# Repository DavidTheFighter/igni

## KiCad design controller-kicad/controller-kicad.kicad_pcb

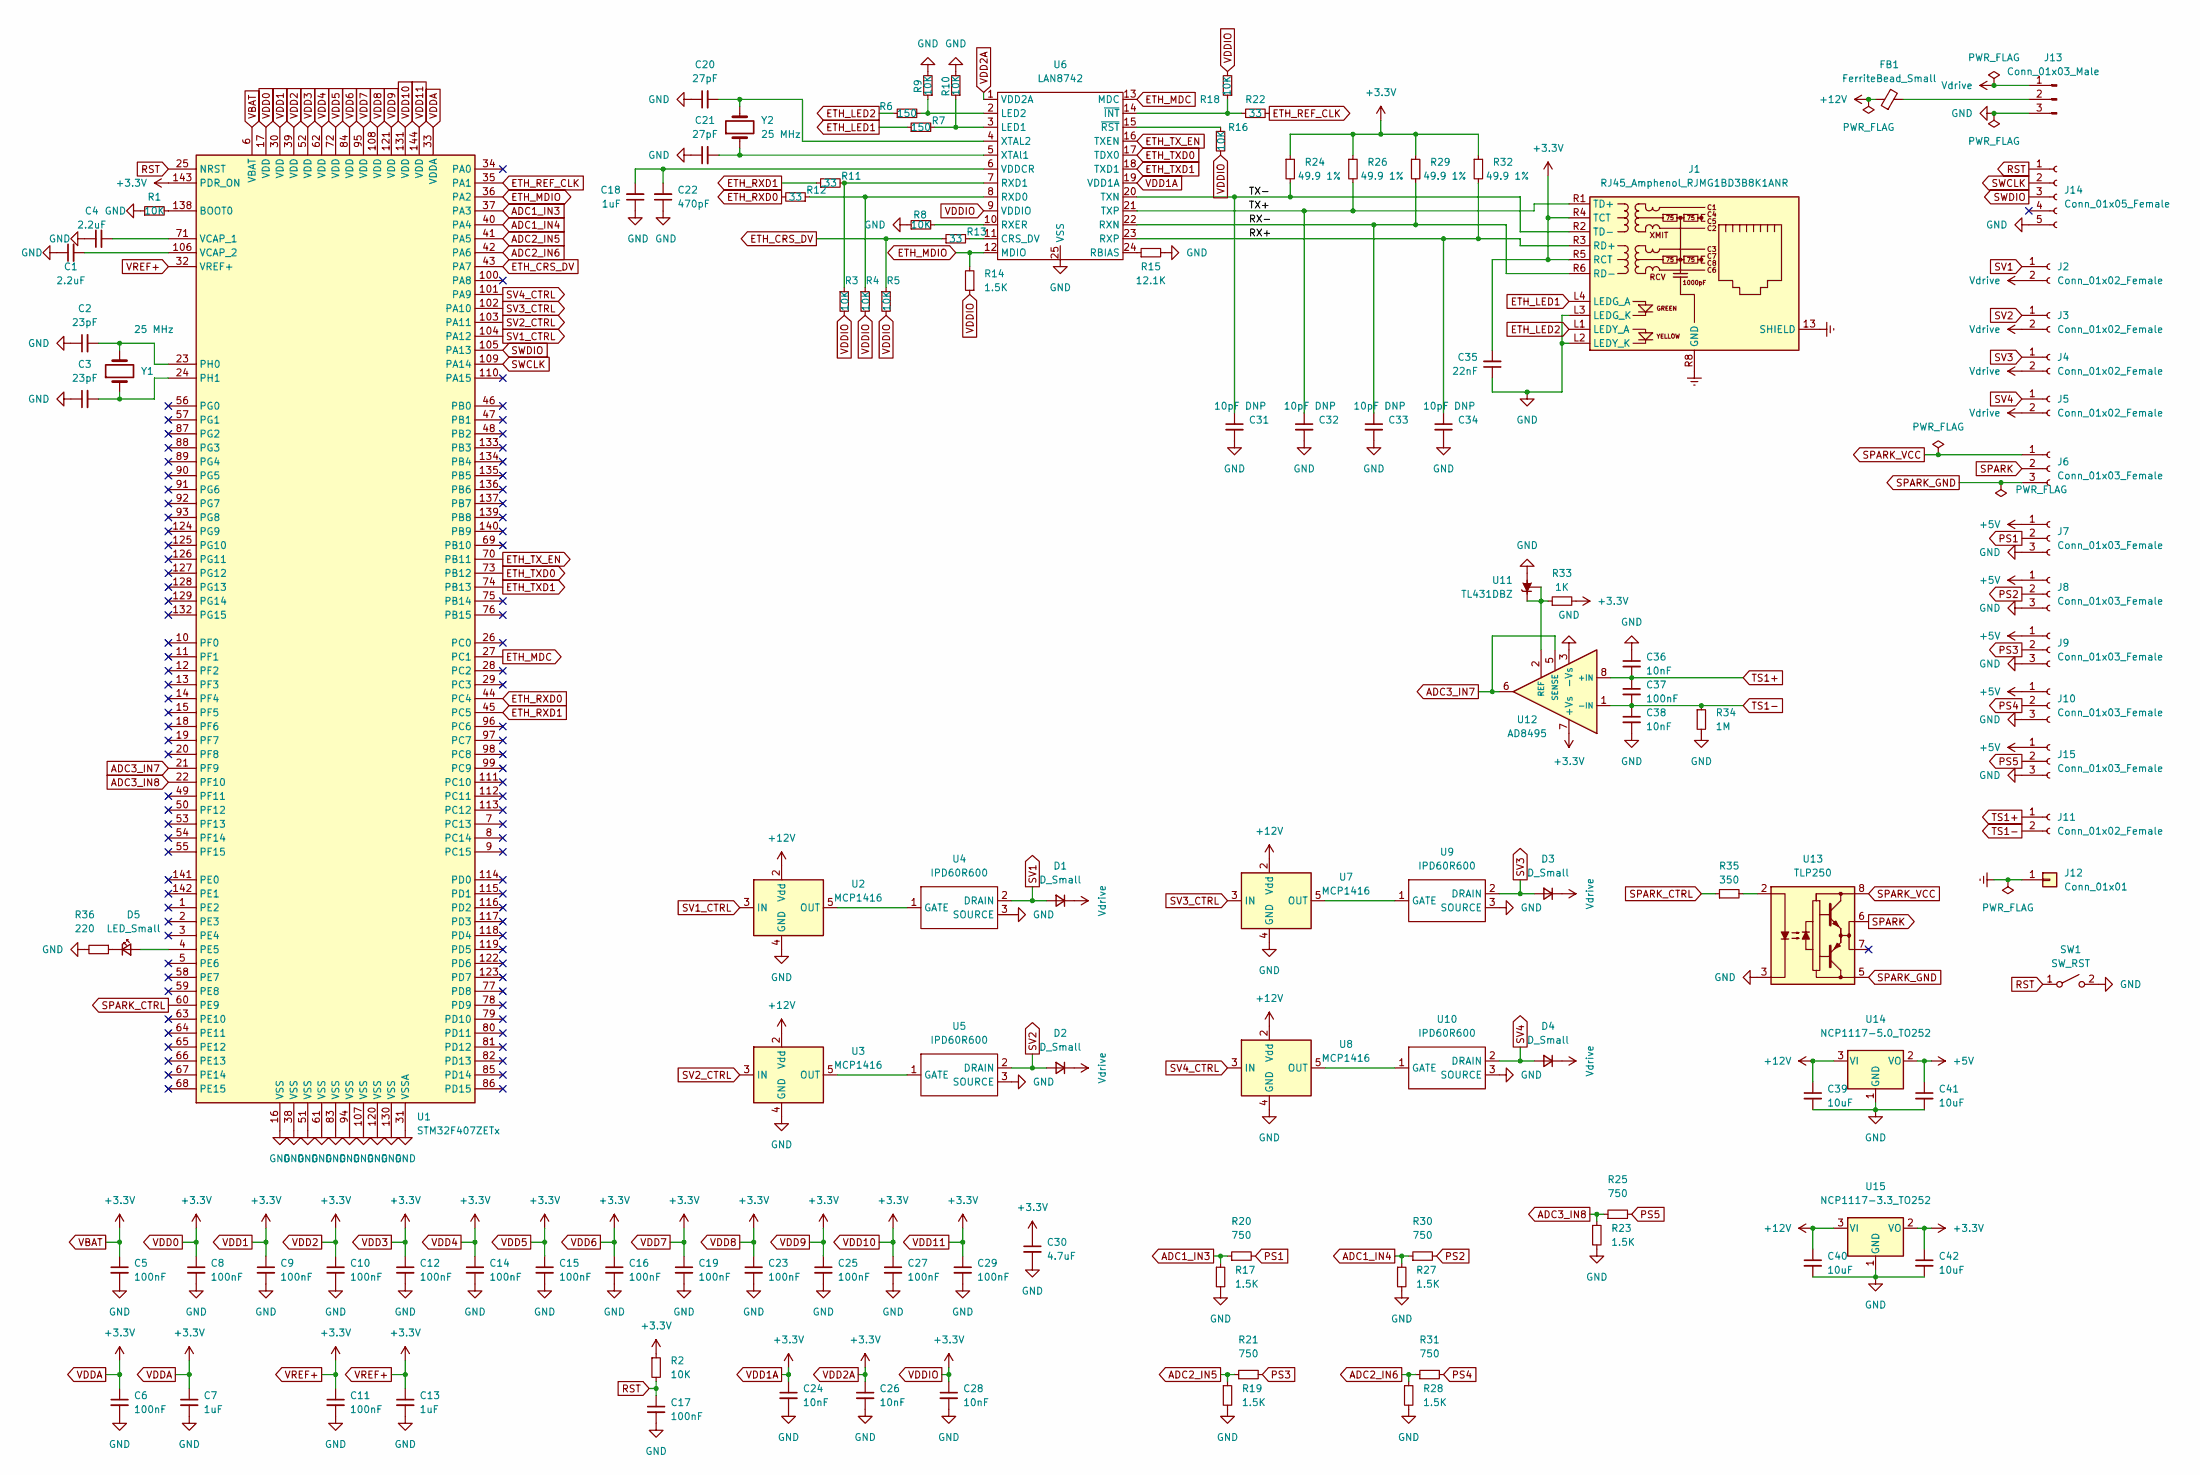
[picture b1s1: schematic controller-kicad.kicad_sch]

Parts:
C1, C4: 2.2uF; C_0603_1608Metric_Pad1.08x0.95mm_HandSolder
C2, C3: 23pF; C_0603_1608Metric_Pad1.08x0.95mm_HandSolder
C5, C6, C8, C9, C10, C11, C12, C14, C15, C16, C17, C19, C23, C25, C27, C29, C37: 100nF; C_0603_1608Metric_Pad1.08x0.95mm_HandSolder
C7, C13, C18: 1uF; C_0603_1608Metric_Pad1.08x0.95mm_HandSolder
C20, C21: 27pF; C_0603_1608Metric_Pad1.08x0.95mm_HandSolder
C22: 470pF; C_0603_1608Metric_Pad1.08x0.95mm_HandSolder
C24, C26, C28, C36, C38: 10nF; C_0603_1608Metric_Pad1.08x0.95mm_HandSolder
C30: 4.7uF; C_0603_1608Metric_Pad1.08x0.95mm_HandSolder
C31, C32, C33, C34: 10pF DNP; C_0603_1608Metric_Pad1.08x0.95mm_HandSolder
C35: 22nF; C_0603_1608Metric_Pad1.08x0.95mm_HandSolder
C39, C40, C41, C42: 10uF; C_0603_1608Metric_Pad1.08x0.95mm_HandSolder
D1, D2, D3, D4: D_Small; D_SMA-SMB_Universal_Handsoldering
D5: LED_Small; LED_0603_1608Metric_Pad1.05x0.95mm_HandSolder
FB1: FerriteBead_Small; C_0603_1608Metric_Pad1.08x0.95mm_HandSolder
J1: RJ45_Amphenol_RJMG1BD3B8K1ANR
J2, J3, J4, J5, J11: Conn_01x02_Female; JST_PH_S2B-PH-SM4-TB_1x02-1MP_P2.00mm_Horizontal
J6, J7, J8, J9, J10, J15: Conn_01x03_Female; JST_PH_S3B-PH-SM4-TB_1x03-1MP_P2.00mm_Horizontal
J12: Conn_01x01; PinHeader_1x01_P2.54mm_Vertical
J13: Conn_01x03_Male; JST_VH_B3P-VH-B_1x03_P3.96mm_Vertical
J14: Conn_01x05_Female; JST_PH_B5B-PH-K_1x05_P2.00mm_Vertical
R1, R2, R3, R4, R5, R8, R9, R10, R16, R18: 10K; R_0603_1608Metric_Pad0.98x0.95mm_HandSolder
R6, R7: 150; R_0603_1608Metric_Pad0.98x0.95mm_HandSolder
R11, R12, R13, R22: 33; R_0603_1608Metric_Pad0.98x0.95mm_HandSolder
R14, R17, R19, R23, R27, R28: 1.5K; R_0603_1608Metric_Pad0.98x0.95mm_HandSolder
R15: 12.1K; R_0603_1608Metric_Pad0.98x0.95mm_HandSolder
R20, R21, R25, R30, R31: 750; R_0603_1608Metric_Pad0.98x0.95mm_HandSolder
R24, R26, R29, R32: 49.9 1%; R_0603_1608Metric_Pad0.98x0.95mm_HandSolder
R33: 1K; R_0603_1608Metric_Pad0.98x0.95mm_HandSolder
R34: 1M; R_0603_1608Metric_Pad0.98x0.95mm_HandSolder
R35: 350; R_0603_1608Metric_Pad0.98x0.95mm_HandSolder
R36: 220; R_0603_1608Metric_Pad0.98x0.95mm_HandSolder
SW1: SW_RST; SW_SPST_PTS810
U1: STM32F407ZETx; LQFP-144_20x20mm_P0.5mm
U2, U3, U7, U8: MCP1416; SOT-23-5
U4, U5, U9, U10: IPD60R600; TO-252-3_TabPin2-HandSolder
U6: LAN8742; VQFN-24-1EP_4x4mm_P0.5mm_EP2.45x2.45mm
U11: TL431DBZ; SOT-23
U12: AD8495; MSOP-8_3x3mm_P0.65mm
U13: TLP250; DIP-8_W7.62mm
U14: NCP1117-5.0_TO252; TO-252-2
U15: NCP1117-3.3_TO252; TO-252-2
Y1, Y2: 25 MHz; Crystal_SMD_HC49-SD_HandSoldering

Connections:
+5V: C41.1, J7.1, J8.1, J9.1, J10.1, J15.1, U14.2 (VO)
+12V: C39.1, C40.1, FB1.1, U2.2 (Vdd), U3.2 (Vdd), U7.2 (Vdd), U8.2 (Vdd), U14.3 (VI), U15.3 (VI)
/RX+: C34.1, J1.R3 (RD+), R32.2, U6.23 (RXP)
/RX-: C33.1, J1.R6 (RD-), R29.2, U6.22 (RXN)
/TX+: C32.1, J1.R1 (TD+), R26.2, U6.21 (TXP)
/TX-: C31.1, J1.R2 (TD-), R24.2, U6.20 (TXN)
ADC1_IN3: R17.1, R20.1, U1.37 (PA3)
ADC1_IN4: R27.1, R30.1, U1.40 (PA4)
ADC2_IN5: R19.1, R21.1, U1.41 (PA5)
ADC2_IN6: R28.1, R31.1, U1.42 (PA6)
ADC3_IN7: U1.21 (PF9), U12.5 (SENSE), U12.6
ADC3_IN8: R23.1, R25.1, U1.22 (PF10)
ETH_CRS_DV: R5.1, R13.1, U1.43 (PA7)
ETH_LED1: J1.L4 (LEDG_A), R7.1
ETH_LED2: J1.L1 (LEDY_A), R6.1
ETH_MDC: U1.27 (PC1), U6.13 (MDC)
ETH_MDIO: R14.2, U1.36 (PA2), U6.12 (MDIO)
ETH_REF_CLK: R22.2, U1.35 (PA1)
ETH_RXD0: R12.2, U1.44 (PC4)
ETH_RXD1: R11.1, U1.45 (PC5)
ETH_TXD0: U1.73 (PB12), U6.17 (TDX0)
ETH_TXD1: U1.74 (PB13), U6.18 (TXD1)
ETH_TX_EN: U1.70 (PB11), U6.16 (TXEN)
Earth: J1.13 (SHIELD), J1.R8 (GND), J12.1
GND: C1.1, C2.1, C3.1, C4.1, C5.2, C6.2, C7.2, C8.2, C9.2, C10.2, C11.2, C12.2, C13.2, C14.2, C15.2, C16.2, C17.2, C18.1, C19.2, C20.1, C21.1, C22.1, C23.2, C24.2, C25.2, C26.2, C27.2, C28.2, C29.2, C30.2, C31.2, C32.2, C33.2, C34.2, C35.1, C36.1, C38.2, C39.2, C40.2, C41.2, C42.2, J1.L2 (LEDY_K), J1.L3 (LEDG_K), J7.3, J8.3, J9.3, J10.3, J13.3, J14.5, J15.3, R1.1, R8.1, R9.2, R10.2, R15.2, R17.2, R19.2, R23.2, R27.2, R28.2, R34.2, R36.2, SW1.2 (B), U1.16 (VSS), U1.31 (VSSA), U1.38 (VSS), U1.51 (VSS), U1.61 (VSS), U1.83 (VSS), U1.94 (VSS), U1.107 (VSS), U1.120 (VSS), U1.130 (VSS), U2.4 (GND), U3.4 (GND), U4.3 (SOURCE), U5.3 (SOURCE), U6.25 (VSS), U7.4 (GND), U8.4 (GND), U9.3 (SOURCE), U10.3 (SOURCE), U11.3 (A), U12.3 (-Vs), U13.3 (C), U14.1 (GND), U15.1 (GND)
unnamed: C1.2, U1.106 (VCAP_2)
unnamed: C2.2, U1.23 (PH0), Y1.2
unnamed: C3.2, U1.24 (PH1), Y1.1
unnamed: C4.2, U1.71 (VCAP_1)
unnamed: C18.2, C22.2, U6.6 (VDDCR)
unnamed: C20.2, U6.4 (XTAL2), Y2.2
unnamed: C21.2, U6.5 (XTAl1), Y2.1
unnamed: D5.1 (K), R36.1
unnamed: D5.2 (A), U1.4 (PE5)
unnamed: FB1.2, J13.2
unnamed: R1.2, U1.138 (BOOT0)
unnamed: R6.2, R9.1, U6.2 (LED2)
unnamed: R8.2, U6.10 (RXER)
unnamed: R7.2, R10.1, U6.3 (LED1)
unnamed: R3.1, R11.2, U6.7 (RXD1)
unnamed: R4.1, R12.1, U6.8 (RXD0)
unnamed: R13.2, U6.11 (CRS_DV)
unnamed: R15.1, U6.24 (RBIAS)
unnamed: R16.1, U6.15 (~RST)
unnamed: R18.1, R22.1, U6.14 (~INT)
unnamed: R33.1, U11.1 (K), U11.2 (REF), U12.2 (REF)
unnamed: R35.2, U13.2 (A)
unnamed: U2.5 (OUT), U4.1 (GATE)
unnamed: U3.5 (OUT), U5.1 (GATE)
unnamed: U7.5 (OUT), U9.1 (GATE)
unnamed: U8.5 (OUT), U10.1 (GATE)
PS1: J7.2, R20.2
PS2: J8.2, R30.2
PS3: J9.2, R21.2
PS4: J10.2, R31.2
PS5: J15.2, R25.2
RST: C17.1, J14.1, R2.2, SW1.1 (A), U1.25 (NRST)
SPARK: J6.2, U13.6 (VO)
SPARK_CTRL: R35.1, U1.60 (PE9)
SPARK_GND: J6.3, U13.5 (VEE)
SPARK_VCC: J6.1, U13.8 (VCC)
SV1: D1.2 (A), J2.1, U4.2 (DRAIN)
SV1_CTRL: U1.104 (PA12), U2.3 (IN)
SV2: D2.2 (A), J3.1, U5.2 (DRAIN)
SV2_CTRL: U1.103 (PA11), U3.3 (IN)
SV3: D3.2 (A), J4.1, U9.2 (DRAIN)
SV3_CTRL: U1.102 (PA10), U7.3 (IN)
SV4: D4.2 (A), J5.1, U10.2 (DRAIN)
SV4_CTRL: U1.101 (PA9), U8.3 (IN)
SWCLK: J14.2, U1.109 (PA14)
SWDIO: J14.3, U1.105 (PA13)
TS1+: C36.2, C37.1, J11.1, U12.8 (+IN)
TS1-: C37.2, C38.1, J11.2, R34.1, U12.1 (-IN)
VBAT: C5.1, C6.1, C7.1, C8.1, C9.1, C10.1, C11.1, C12.1, C13.1, C14.1, C15.1, C16.1, C19.1, C23.1, C24.1, C25.1, C26.1, C27.1, C28.1, C29.1, C30.1, C35.2, C42.1, J1.R4 (TCT), J1.R5 (RCT), R2.1, R3.2, R4.2, R5.2, R14.1, R16.2, R18.2, R24.1, R26.1, R29.1, R32.1, R33.2, U1.6 (VBAT), U1.17 (VDD), U1.30 (VDD), U1.32 (VREF+), U1.33 (VDDA), U1.39 (VDD), U1.52 (VDD), U1.62 (VDD), U1.72 (VDD), U1.84 (VDD), U1.95 (VDD), U1.108 (VDD), U1.121 (VDD), U1.131 (VDD), U1.143 (PDR_ON), U1.144 (VDD), U6.1 (VDD2A), U6.9 (VDDIO), U6.19 (VDD1A), U12.7 (+Vs), U15.2 (VO)
Vdrive: D1.1 (K), D2.1 (K), D3.1 (K), D4.1 (K), J2.2, J3.2, J4.2, J5.2, J13.1

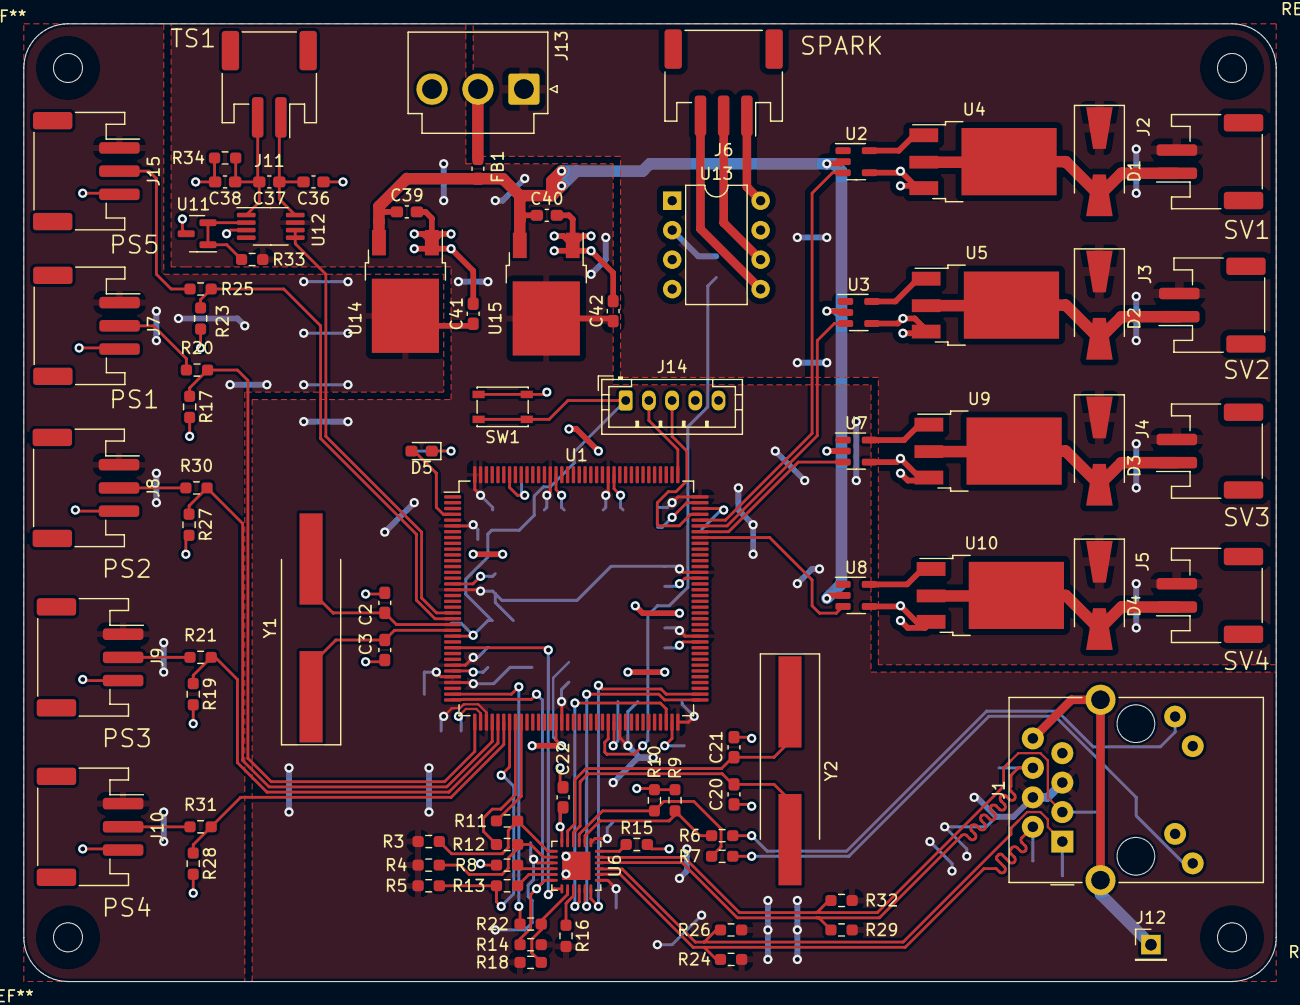
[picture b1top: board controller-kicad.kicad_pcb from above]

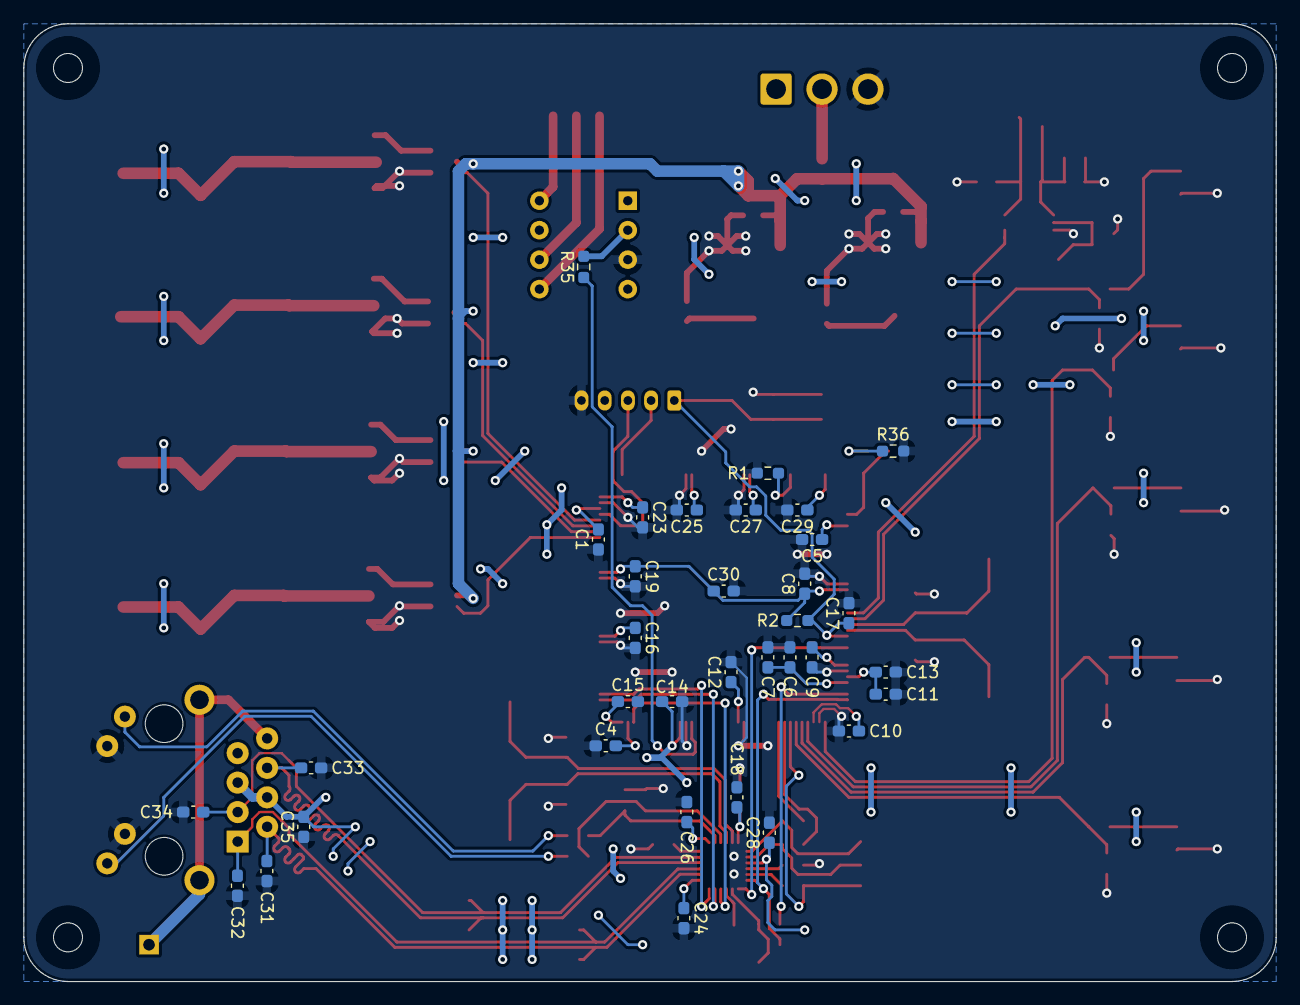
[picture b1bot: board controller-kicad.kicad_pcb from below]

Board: 2 copper layers, 108.0 x 82.5 mm, 117 parts (34 on the bottom side), 75 nets.

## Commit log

2022-10-26 Added some initial STM32 pins & caps
2022-10-26 Started mosfets
2022-10-31 Mostly finished LAN8742 circuit
2022-11-01 Finishing up ECU schematic
2022-11-03 Started routing PCB
2022-11-04 More progress on routing
2022-11-07 Got all components onto PCB
2022-11-08 Routing mostly finished
2022-11-12 Added reset button to PCB
2022-11-14 Hopefully finished board
